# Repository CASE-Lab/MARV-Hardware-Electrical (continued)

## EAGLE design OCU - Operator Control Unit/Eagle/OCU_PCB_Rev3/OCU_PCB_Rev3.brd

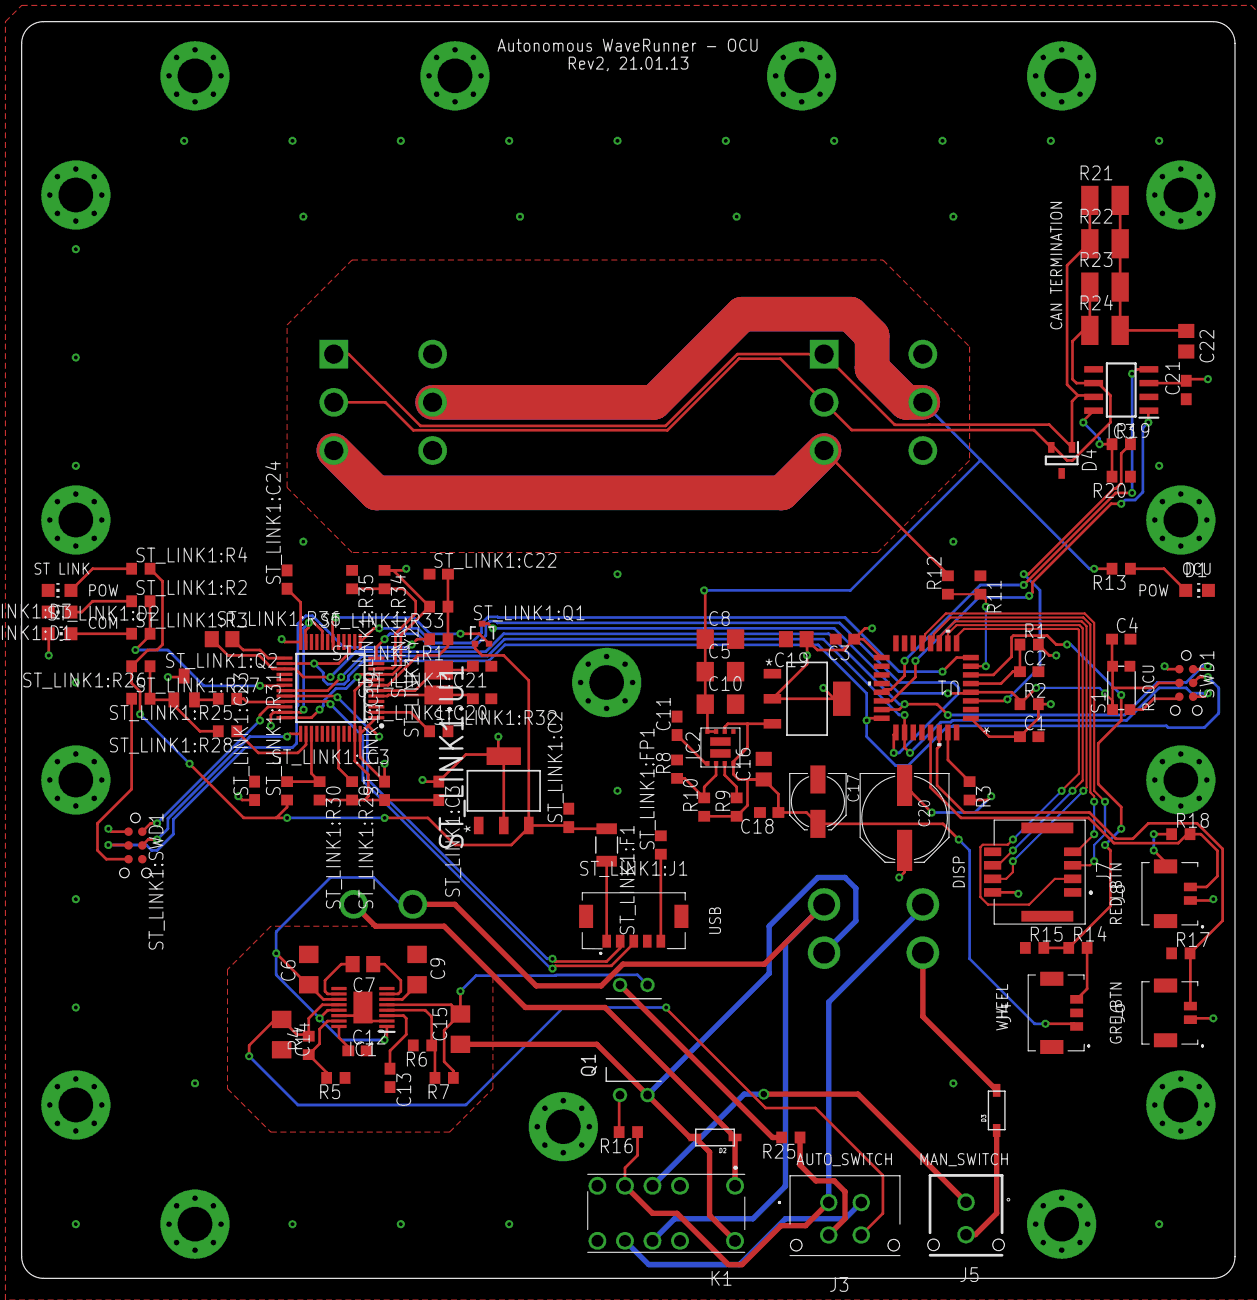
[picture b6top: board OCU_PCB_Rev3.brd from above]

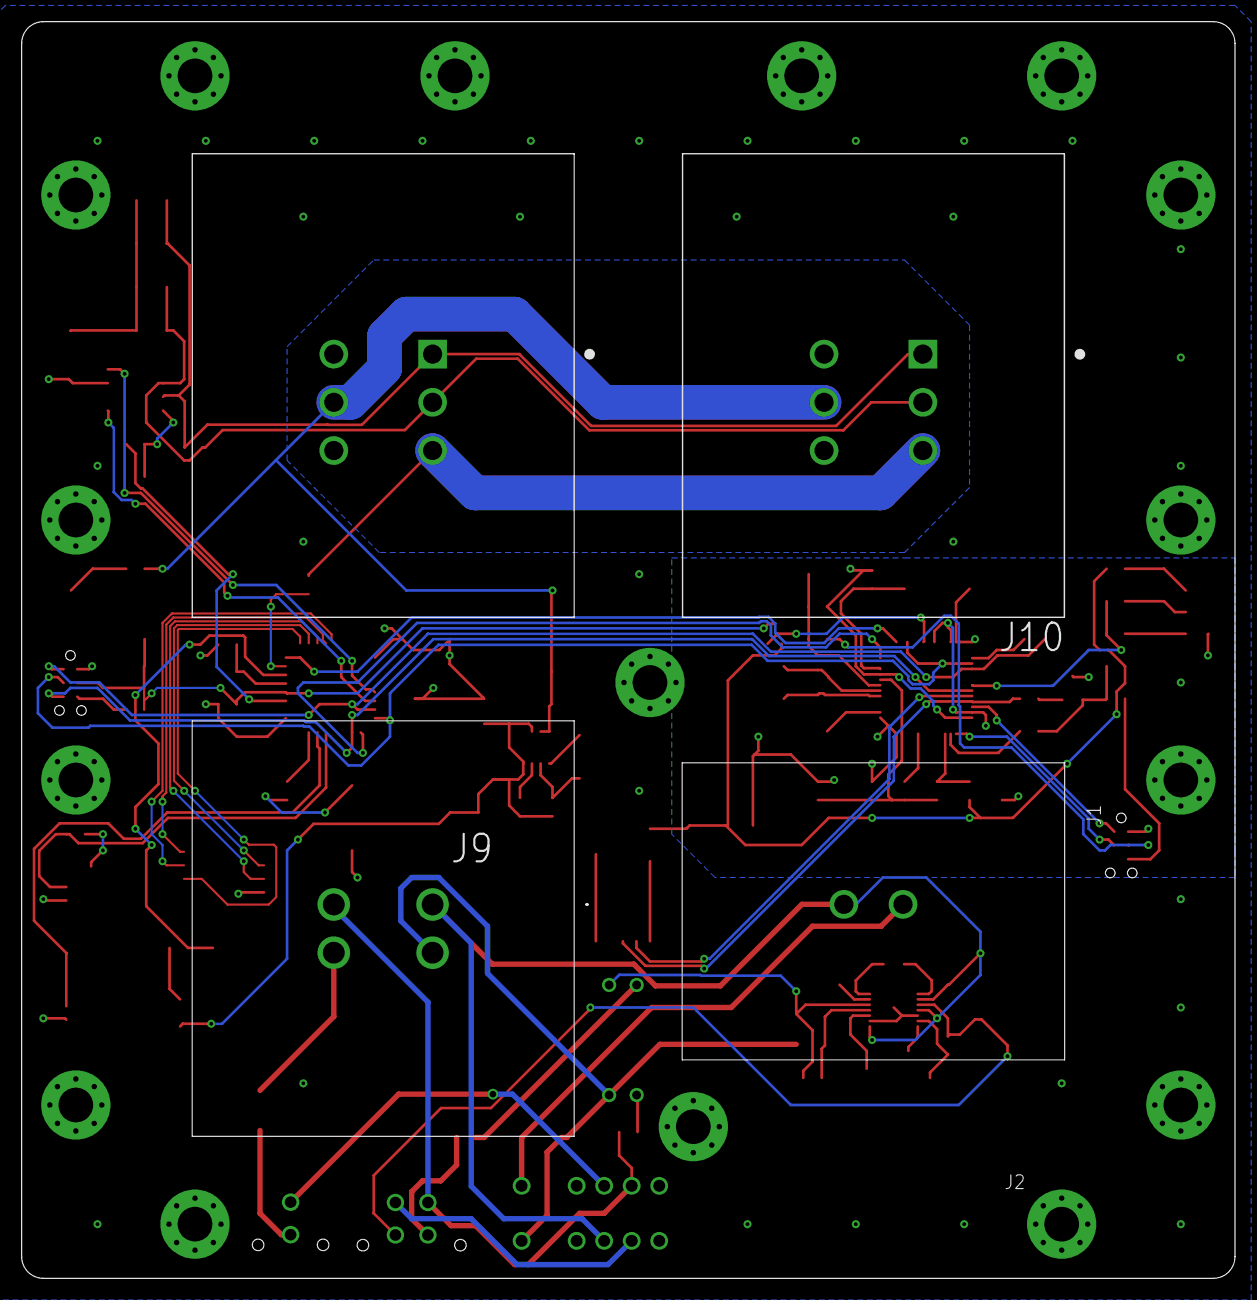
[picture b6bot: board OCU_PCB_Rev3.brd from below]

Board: 2 copper layers, 112.0 x 116.0 mm, 122 parts (4 on the bottom side), 79 nets.

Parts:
C1, C2, C3, C4, C21: 0.1uF; C0603
C5, C6, C8, C9, C10, C14, C15: 10uF; C1206
C7: 1uF; C0805
C11: 3.3nF; C0603
C12, C13: 10nF; C0603
C16: 22uF; C0805
C17: 100uF; PANASONIC_C
C18: 100nF; C0603
C19: 10uF; C0805
C20: 220uF; PANASONIC_E
C22: 4.7nF; C0805
D1: 12V-POW; CHIP-LED0805
D2, D3: SOD-123
D4: SZNUP2105LT1G; SOT96P237X111-3N
HOLE1, HOLE2, HOLE3, HOLE4, HOLE5, HOLE6, HOLE7, HOLE8, HOLE9, HOLE10, HOLE11, HOLE12, HOLE13, HOLE14, HOLE15, HOLE16: M3_MOUNTING_HOLE
IC1: LTC3260EMSE#PBF; SOP50P490X110-17N
IC2: LMZ21700SILT; SIL0008E
IC3: SN65HVD230DR; SOT127P600X175-8N
J1: DT15-2P; DT152P
J2: DT15-4P; DT154P
J3: 43045-0413; 430450413
J4: 505567-0371; 5055680371
J5: 43045-0213
J6, J8: 505567-0271; 5055680271
J7: 505433-0871; 5054330871
J9, J10: DT15-6P; TE_DT15-6P
K1: V23079A1003B301; 413937885
Q1: VO618A-3; DIL04-400
R1: BLM18PG471SN1D; R0603
R2, R3, R17, R18: 10K; R0603
R4, R7: 909K; R0603
R5, R6: 100K; R0603
R8: 44K2 1%; R0603
R9: 10K 1%; R0603
R10: 232K 1%; R0603
R11: 3K9; R0603
R12: 15K; R0603
R13: 820R; R0603
R14: 4K7; R0603
R15: 9K1; R0603
R16: 1K5; R0603
R19: -; R0603
R20, R25: 0R; R0603
R21, R22, R23, R24: 120R; R1210
S1: KMR621NGLFS
ST_LINK1:C2, ST_LINK1:C19, ST_LINK1:C22, ST_LINK1:C23, ST_LINK1:C24: 0.1uF; C0603
ST_LINK1:C3: 10uF; C0603
ST_LINK1:C20, ST_LINK1:C21: 10pF; C0603
ST_LINK1:D1, ST_LINK1:D2, ST_LINK1:D3: CHIP-LED0805
ST_LINK1:F1: OZCJ0050; OZCJ
ST_LINK1:FP1: R0603
ST_LINK1:IC3: STM32F103CBT6TR; QFP50P900X900X160-48N
ST_LINK1:J1: 505568-0571; 5055680571
ST_LINK1:Q1: 2N7002PW,115; SOT323
ST_LINK1:Q2: BC817; SOT23
ST_LINK1:R1: 0; R0603
ST_LINK1:R2, ST_LINK1:R3: 330; R0603
ST_LINK1:R4: 680; R0603
ST_LINK1:R25: 1K5; R0603
ST_LINK1:R26, ST_LINK1:R32: 10K; R0603
ST_LINK1:R27: 36K; R0603
ST_LINK1:R28: 100; R0603
ST_LINK1:R29, ST_LINK1:R33: 100K; R0603
ST_LINK1:R30, ST_LINK1:R34, ST_LINK1:R35: 4K7; R0603
ST_LINK1:R31: 2K7; R0603
ST_LINK1:R36: 100; R0805
ST_LINK1:SWD1: SWD_TAGCONNECTNO-LEG; TC2030-IDC-NL
ST_LINK1:U1: LD1117S33TR; SOT230P700X180-4N
ST_LINK1:Y2: NX3225GD-8MHZ-STD-CRA-3; RESC3226X100N
SWD1: SWD_TAGCONNECTNO-LEG; TC2030-IDC-NL
U1: STM32F303K8; LQFP-32
U2: LD1117S33TR; SOT230P700X180-4N

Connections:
12V: C5.1, C8.1, C10.1, IC2.7, IC2.8, J9.5, J10.5, R13.2
+3V3: C1.1, C3.1, C19.1, C20.+, C21.2, IC3.3, J6.1, J7.2, J8.1, R1.2, R2.2, SWD1.1, U1.1, U1.17, U2.2, U2.4
+5V: C16.1, C17.+, C18.1, IC2.4, IC2.6, J4.1, R9.1, R10.1, U2.3
+12V: J9.3, J10.3, R12.2
+24V: C14.1, IC1.12, J3.4, R4.2
BTN_GRE: J6.2, R17.2, U1.30
BTN_RED: J8.2, R18.2, U1.29
CAN_N: D4.2, IC3.6, J9.2, J10.2, R23.1, R24.1
CAN_N1: D4.1, IC3.7, J9.1, J10.1, R21.1, R22.1
D: IC3.1, U1.22
DISP_CS: J7.6, U1.10
DISP_DC: J7.3, U1.9
DISP_DIN: J7.5, U1.13
DISP_RST: J7.7, U1.12
DISP_SCLK: J7.4, U1.11
GND: C1.2, C2.2, C3.2, C4.2, C5.2, C8.2, C10.2, C11.2, C16.2, C17.-, C18.2, C19.2, C20.-, C21.1, C22.2, D1.C, D4.3, IC2.5, IC2.9, IC2.10, IC3.2, J4.2, J4.MP1, J4.MP2, J6.MP1, J6.MP2, J7.1, J7.MP1, J7.MP2, J8.MP1, J8.MP2, J9.4, J9.6, J10.4, J10.6, R3.2, R8.2, R11.1, R15.1, R17.1, R18.1, R20.1, S1.1, S1.2, ST_LINK1:C2.2, ST_LINK1:C3.2, ST_LINK1:C19.1, ST_LINK1:C20.1, ST_LINK1:C21.1, ST_LINK1:C22.1, ST_LINK1:C23.2, ST_LINK1:C24.2, ST_LINK1:D1.C, ST_LINK1:D3.C, ST_LINK1:FP1.2, ST_LINK1:IC3.8, ST_LINK1:IC3.20, ST_LINK1:IC3.23, ST_LINK1:IC3.35, ST_LINK1:IC3.47, ST_LINK1:J1.4, ST_LINK1:J1.MP1, ST_LINK1:J1.MP2, ST_LINK1:R27.1, ST_LINK1:R29.2, ST_LINK1:R30.2, ST_LINK1:R32.2, ST_LINK1:R35.1, ST_LINK1:SWD1.5, ST_LINK1:U1.1, SWD1.5, U1.16, U1.32, U2.1
GNDA: C15.2, IC1.5, Q1.3, R7.1
MAN_S_IN: J5.1, K1.4
MAN_S_OUT: J2.4, J3.1, K1.5, R16.1
MODE_LED: J3.3, R25.1
unnamed: J4.3, R14.2
unnamed: C7.1, IC1.7
unnamed: C7.2, IC1.10
unnamed: C22.1, R21.2, R22.2, R23.2, R24.2
unnamed: IC2.2, R8.1, R10.2
unnamed: C11.1, IC2.1
unnamed: C12.1, IC1.16
unnamed: C13.1, IC1.3
unnamed: D3.C, J5.2
unnamed: D1.A, R13.1
unnamed: IC2.3, R9.2
unnamed: J3.2, K1.8
unnamed: C9.2, IC1.6
unnamed: IC1.15, R4.1, R5.2
unnamed: IC3.8, R19.1, R20.2
unnamed: IC1.4, R6.1, R7.2
unnamed: Q1.4, R25.2
unnamed: D3.A, J2.3
unnamed: Q1.1, R16.2
unnamed: D2.C, J1.2, K1.1
unnamed: C2.1, R1.1, U1.5
unnamed: R3.1, U1.31
NRST: C4.1, R2.1, S1.3, S1.4, ST_LINK1:Q1.3, SWD1.3, U1.4
R: IC3.4, U1.21
RS: R19.2, U1.3
RX2: ST_LINK1:IC3.12, U1.25
STM_12_INDIC: R11.2, R12.1, U1.7
ST_LINK1:+3V3: ST_LINK1:C3.1, ST_LINK1:C19.2, ST_LINK1:C23.1, ST_LINK1:C24.1, ST_LINK1:D2.A, ST_LINK1:IC3.1, ST_LINK1:IC3.9, ST_LINK1:IC3.24, ST_LINK1:IC3.36, ST_LINK1:IC3.48, ST_LINK1:Q2.3, ST_LINK1:R33.2, ST_LINK1:R34.1, ST_LINK1:SWD1.1, ST_LINK1:U1.2, ST_LINK1:U1.4
ST_LINK1:+5V: ST_LINK1:C2.1, ST_LINK1:F1.1, ST_LINK1:Q1.1, ST_LINK1:R4.2, ST_LINK1:R26.2, ST_LINK1:R31.1, ST_LINK1:U1.3
ST_LINK1:N$1: ST_LINK1:D1.A, ST_LINK1:R2.1
ST_LINK1:N$2: ST_LINK1:D3.A, ST_LINK1:R4.1
ST_LINK1:N$3: ST_LINK1:D2.C, ST_LINK1:R3.1
ST_LINK1:N$4: ST_LINK1:FP1.1, ST_LINK1:J1.5
ST_LINK1:N$7: ST_LINK1:Q2.2, ST_LINK1:R25.2
ST_LINK1:N$8: ST_LINK1:Q2.1, ST_LINK1:R26.1, ST_LINK1:R27.2, ST_LINK1:R28.2
ST_LINK1:N$15: ST_LINK1:IC3.39, ST_LINK1:R30.1, ST_LINK1:R31.2
ST_LINK1:N$16: ST_LINK1:IC3.2, ST_LINK1:R32.1
ST_LINK1:N$21: ST_LINK1:IC3.44, ST_LINK1:R29.1
ST_LINK1:N$22: ST_LINK1:C20.2, ST_LINK1:IC3.5, ST_LINK1:Y2.1
ST_LINK1:N$23: ST_LINK1:IC3.10, ST_LINK1:R34.2, ST_LINK1:R35.2
ST_LINK1:N$24: ST_LINK1:C21.2, ST_LINK1:IC3.6, ST_LINK1:Y2.2
ST_LINK1:N$25: ST_LINK1:C22.2, ST_LINK1:IC3.7, ST_LINK1:R1.1, ST_LINK1:R33.1
ST_LINK1:N$26: ST_LINK1:IC3.25, ST_LINK1:R36.2
ST_LINK1:N$27: ST_LINK1:F1.2, ST_LINK1:J1.1
ST_LINK1:NRST: ST_LINK1:IC3.18, ST_LINK1:Q1.2
ST_LINK1:STLK_LED: ST_LINK1:IC3.30, ST_LINK1:R2.2, ST_LINK1:R3.2
ST_LINK1:STM_NRST: ST_LINK1:R1.2, ST_LINK1:SWD1.3
ST_LINK1:STM_SWCLK: ST_LINK1:IC3.37, ST_LINK1:SWD1.4
ST_LINK1:STM_SWDIO: ST_LINK1:IC3.34, ST_LINK1:SWD1.2
ST_LINK1:USB_D_N: ST_LINK1:IC3.32, ST_LINK1:J1.2
ST_LINK1:USB_D_P: ST_LINK1:IC3.33, ST_LINK1:J1.3, ST_LINK1:R25.1
ST_LINK1:USB_RENUM: ST_LINK1:IC3.38, ST_LINK1:R28.1
SWDCLK: ST_LINK1:IC3.15, ST_LINK1:IC3.26, SWD1.4, U1.24
SWDIO: ST_LINK1:IC3.27, ST_LINK1:R36.1, SWD1.2, U1.23
SWO: ST_LINK1:IC3.31, SWD1.6, U1.26
S_12V: C6.1, IC1.1, IC1.11, IC1.13, J1.1, J2.1, K1.9
S_GND: C6.2, C9.1, C12.2, C13.2, C14.2, C15.1, D2.A, IC1.2, IC1.14, IC1.17, J2.2, K1.12, Q1.2, R5.1, R6.2
TX2: ST_LINK1:IC3.13, U1.8
WHEEL: R14.1, R15.2, U1.6

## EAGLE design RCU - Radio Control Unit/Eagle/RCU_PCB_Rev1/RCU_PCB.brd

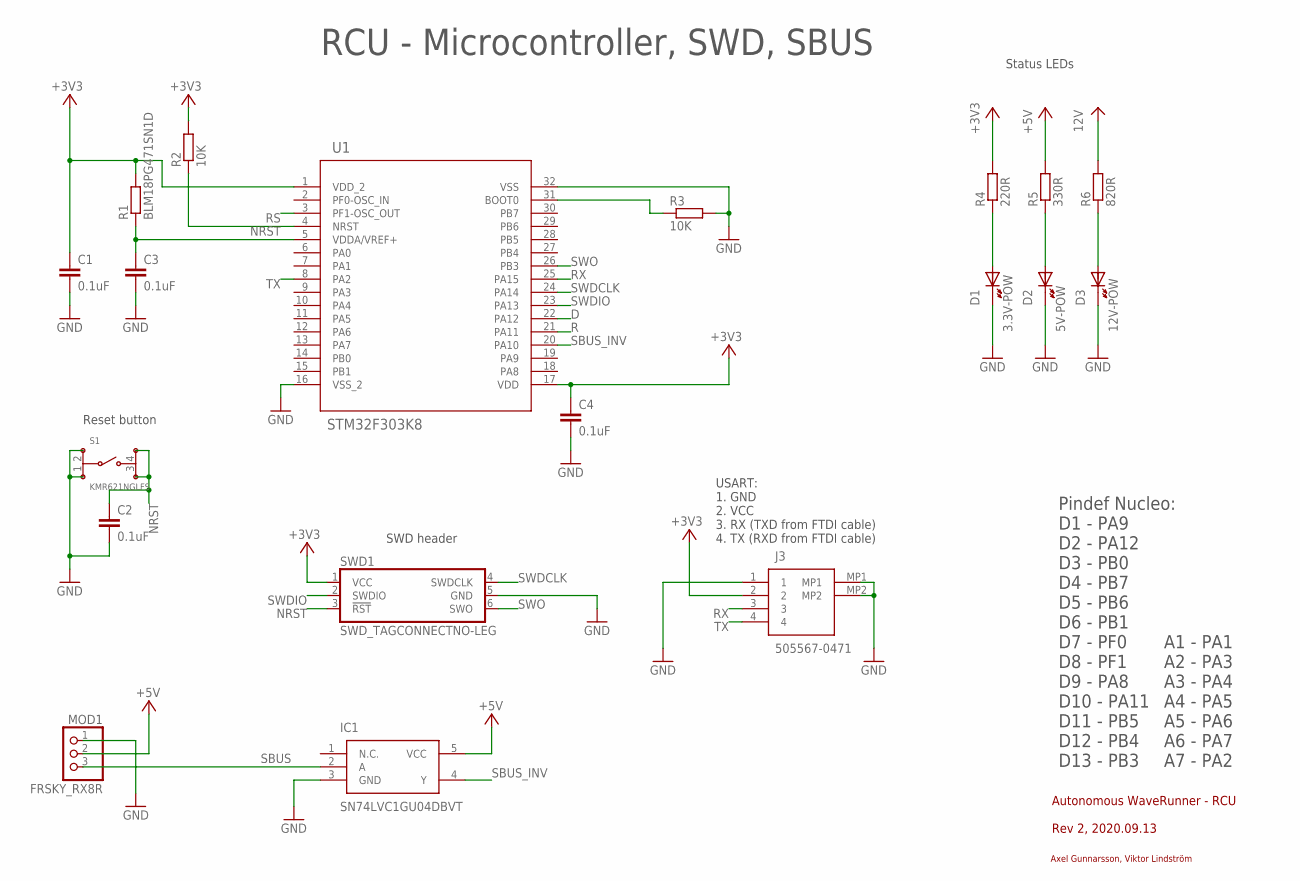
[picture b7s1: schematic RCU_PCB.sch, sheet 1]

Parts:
C1, C2, C3, C4: 0.1uF; C0603
D1: 3.3V-POW; CHIP-LED0805
D2: 5V-POW; CHIP-LED0805
D3: 12V-POW; CHIP-LED0805
IC1: SN74LVC1GU04DBVT; SOT95P280X145-5N
J3: 505567-0471; 5055680471
MOD1: FRSKY_RX8R
R1: BLM18PG471SN1D; R0603
R2, R3: 10K; R0603
R4: 220R; R0603
R5: 330R; R0603
R6: 820R; R0603
S1: KMR621NGLFS
SWD1: SWD_TAGCONNECTNO-LEG; TC2030-IDC-NL
U1: STM32F303K8; LQFP-32

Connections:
12V: R6.2; also elsewhere on the board
+3V3: C1.1, C4.1, J3.2, R1.2, R2.2, R4.2, SWD1.1 (VCC), U1.1 (VDD_2), U1.17 (VDD); also elsewhere on the board
+5V: IC1.5 (VCC), MOD1.2, R5.2; also elsewhere on the board
D: U1.22 (PA12); also elsewhere on the board
GND: C1.2, C2.2, C3.2, C4.2, D1.C (K), D2.C (K), D3.C (K), IC1.3 (GND), J3.1, J3.MP1, J3.MP2, MOD1.1, R3.2, S1.1, S1.2, SWD1.5 (GND), U1.16 (VSS_2), U1.32 (VSS); also elsewhere on the board
unnamed: D3.A, R6.1
unnamed: D2.A, R5.1
unnamed: C3.1, R1.1, U1.5 (VDDA/VREF+)
unnamed: D1.A, R4.1
unnamed: R3.1, U1.31 (BOOT0)
NRST: C2.1, R2.1, S1.3, S1.4, SWD1.3 (!RST), U1.4 (NRST)
R: U1.21 (PA11); also elsewhere on the board
RS: U1.3 (PF1-OSC_OUT); also elsewhere on the board
RX: J3.3, U1.25 (PA15)
SBUS: IC1.2 (A), MOD1.3
SBUS_INV: IC1.4 (Y), U1.20 (PA10)
SWDCLK: SWD1.4 (SWDCLK), U1.24 (PA14)
SWDIO: SWD1.2 (SWDIO), U1.23 (PA13)
SWO: SWD1.6 (SWO), U1.26 (PB3)
TX: J3.4, U1.8 (PA2)

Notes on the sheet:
Autonomous WaveRunner - RCU
Rev 2, 2020.09.13
Axel Gunnarsson, Viktor Lindström
RCU - Microcontroller, SWD, SBUS
SWD header
Reset button
Pindef Nucleo: D1 - PA9 D2 - PA12 D3 - PB0 D4 - PB7 D5 - PB6 D6 - PB1 D7 - PF0 D8 - PF1 D9 - PA8 D10 - PA11 D11 - PB5 D12 - PB4 D13 - PB3
A1 - PA1 A2 - PA3 A3 - PA4 A4 - PA5 A5 - PA6 A6 - PA7 A7 - PA2
Status LEDs
USART: 1. GND 2. VCC 3. RX (TXD from FTDI cable) 4. TX (RXD from FTDI cable)

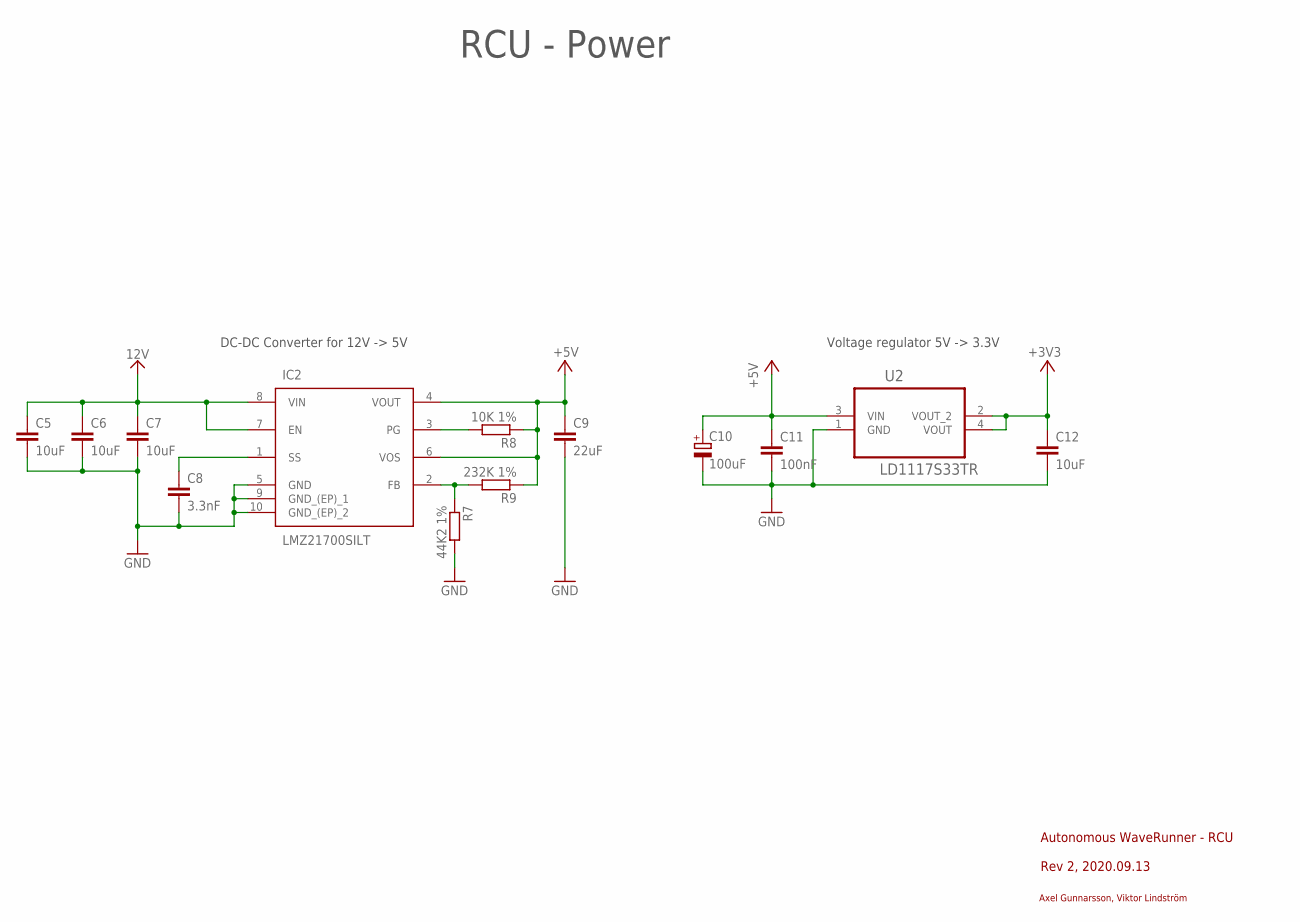
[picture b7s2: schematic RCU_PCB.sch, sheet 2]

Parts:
C5, C6, C7: 10uF; C1206
C8: 3.3nF; C0603
C9: 22uF; C0805
C10: 100uF; PANASONIC_C
C11: 100nF; C0603
C12: 10uF; C0805
IC2: LMZ21700SILT; SIL0008E
R7: 44K2 1%; R0603
R8: 10K 1%; R0603
R9: 232K 1%; R0603
U2: LD1117S33TR; SOT230P700X180-4N

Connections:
12V: C5.1, C6.1, C7.1, IC2.7 (EN), IC2.8 (VIN); also elsewhere on the board
+3V3: C12.1, U2.2 (VOUT_2), U2.4 (VOUT); also elsewhere on the board
+5V: C9.1, C10.+, C11.1, IC2.4 (VOUT), IC2.6 (VOS), R8.1, R9.1, U2.3 (VIN); also elsewhere on the board
GND: C5.2, C6.2, C7.2, C8.2, C9.2, C10.-, C11.2, C12.2, IC2.5 (GND), IC2.9 (GND_(EP)_1), IC2.10 (GND_(EP)_2), R7.2, U2.1 (GND); also elsewhere on the board
unnamed: IC2.2 (FB), R7.1, R9.2
unnamed: C8.1, IC2.1 (SS)
unnamed: IC2.3 (PG), R8.2

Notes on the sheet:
DC-DC Converter for 12V -> 5V
Voltage regulator 5V -> 3.3V
Autonomous WaveRunner - RCU
Rev 2, 2020.09.13
Axel Gunnarsson, Viktor Lindström
RCU - Power

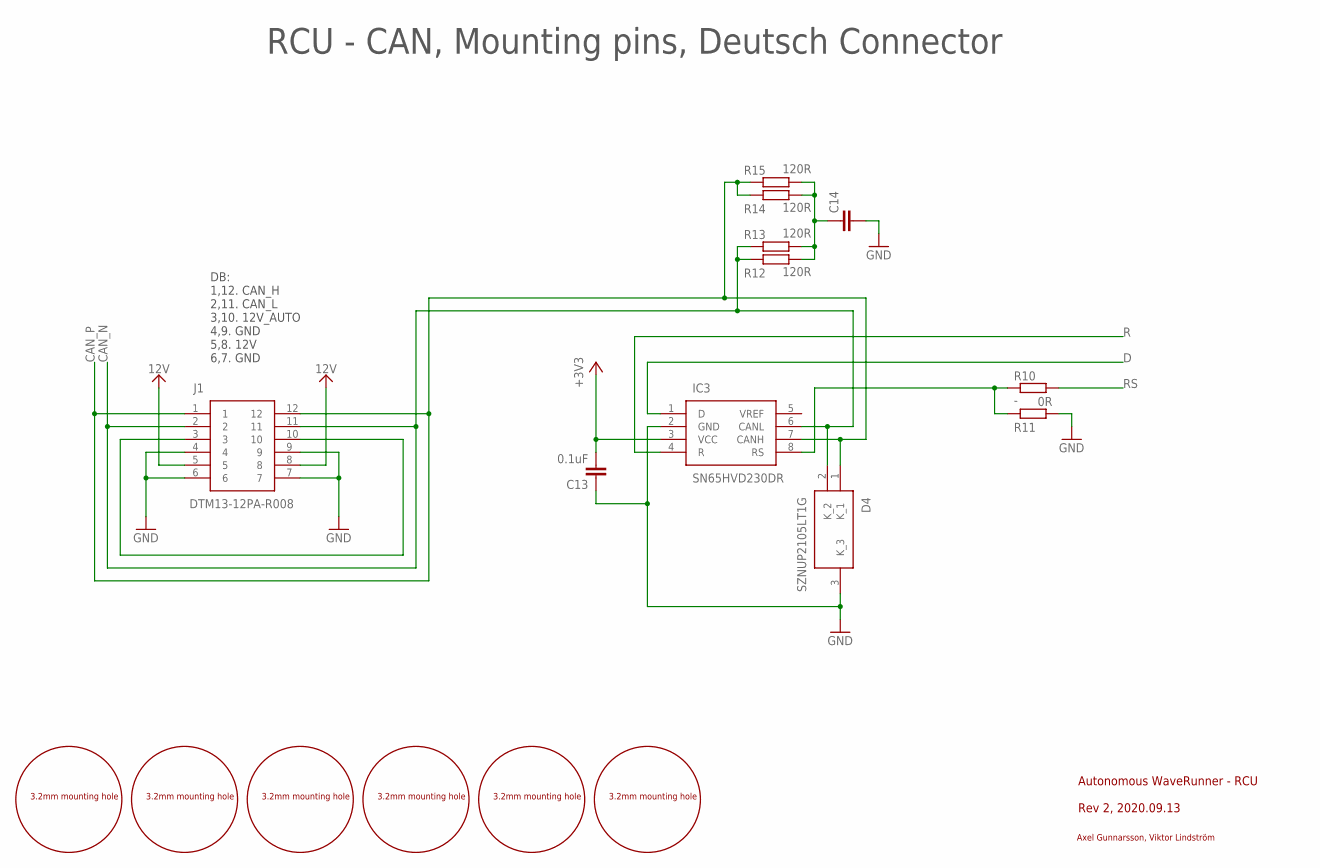
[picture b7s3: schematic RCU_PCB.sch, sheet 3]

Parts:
C13: 0.1uF; C0603
C14: C0805
D4: SZNUP2105LT1G; SOT96P237X111-3N
HOLE1, HOLE2, HOLE3, HOLE4, HOLE5, HOLE6: M3_MOUNTING_HOLE
IC3: SN65HVD230DR; SOT127P600X175-8N
J1: DTM13-12PA-R008; DTM1312PAR008
R10: -; R0603
R11: 0R; R0603
R12, R13, R14, R15: 120R; R1210

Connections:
12V: J1.5, J1.8; also elsewhere on the board
+3V3: C13.2, IC3.3 (VCC); also elsewhere on the board
CAN_N: D4.2 (K_2), IC3.6 (CANL), J1.2, J1.11, R12.1, R13.1
CAN_P: D4.1 (K_1), IC3.7 (CANH), J1.1, J1.12, R14.1, R15.1
D: IC3.1 (D); also elsewhere on the board
GND: C13.1, C14.2, D4.3 (K_3), IC3.2 (GND), J1.4, J1.6, J1.7, J1.9, R11.1; also elsewhere on the board
unnamed: C14.1, R12.2, R13.2, R14.2, R15.2
unnamed: J1.3, J1.10
unnamed: IC3.8 (RS), R10.1, R11.2
R: IC3.4 (R); also elsewhere on the board
RS: R10.2; also elsewhere on the board

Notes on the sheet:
DB: 1,12. CAN_H 2,11. CAN_L 3,10. 12V_AUTO 4,9. GND 5,8. 12V 6,7. GND
Autonomous WaveRunner - RCU
Rev 2, 2020.09.13
Axel Gunnarsson, Viktor Lindström
RCU - CAN, Mounting pins, Deutsch Connector

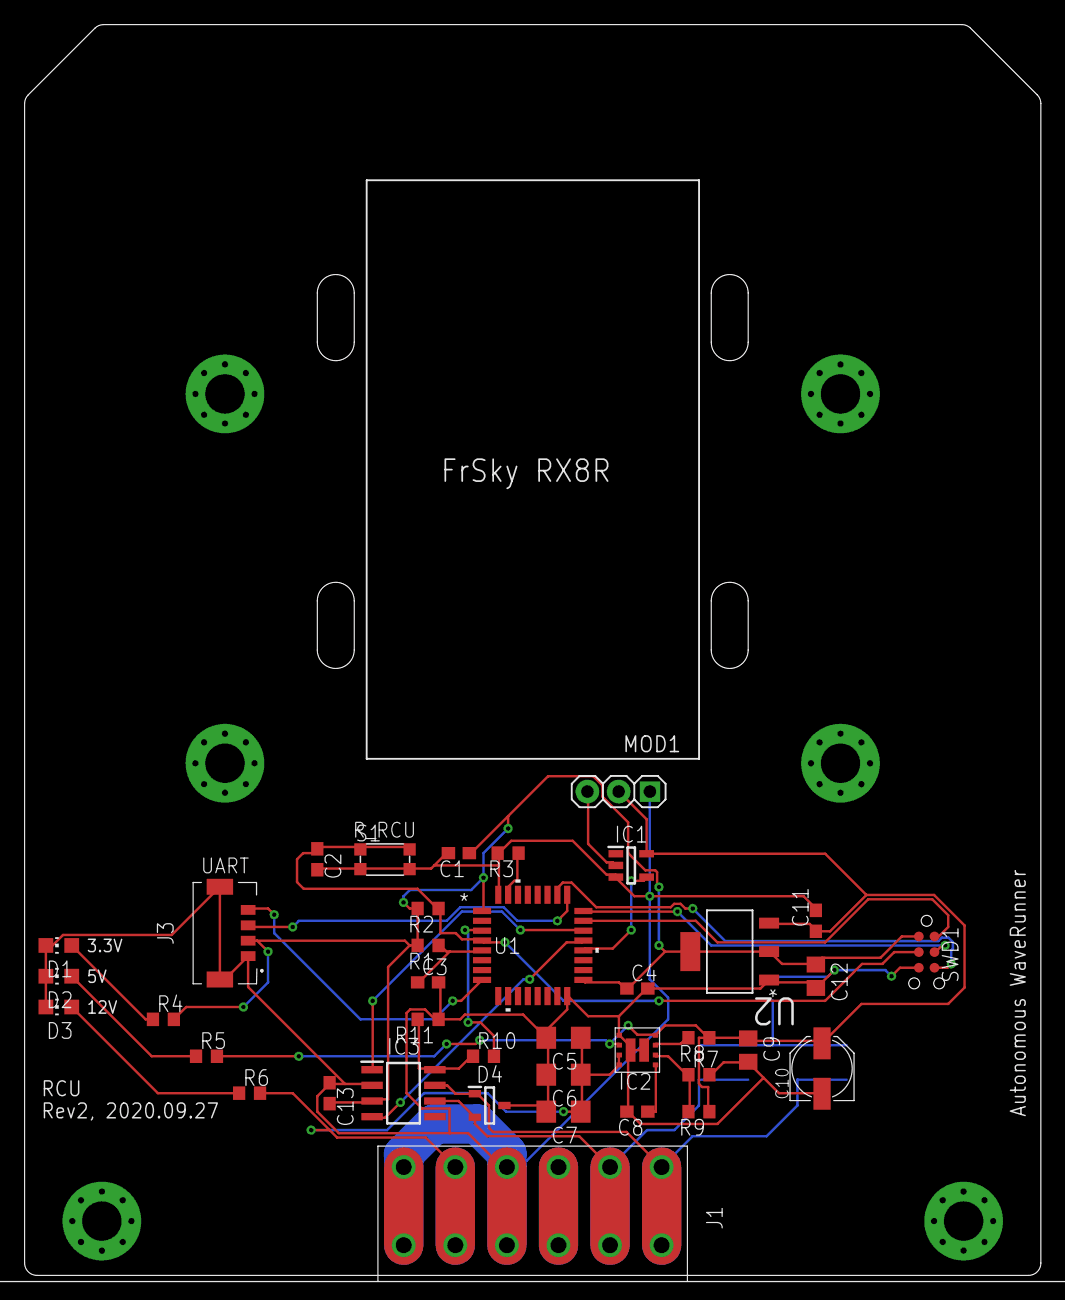
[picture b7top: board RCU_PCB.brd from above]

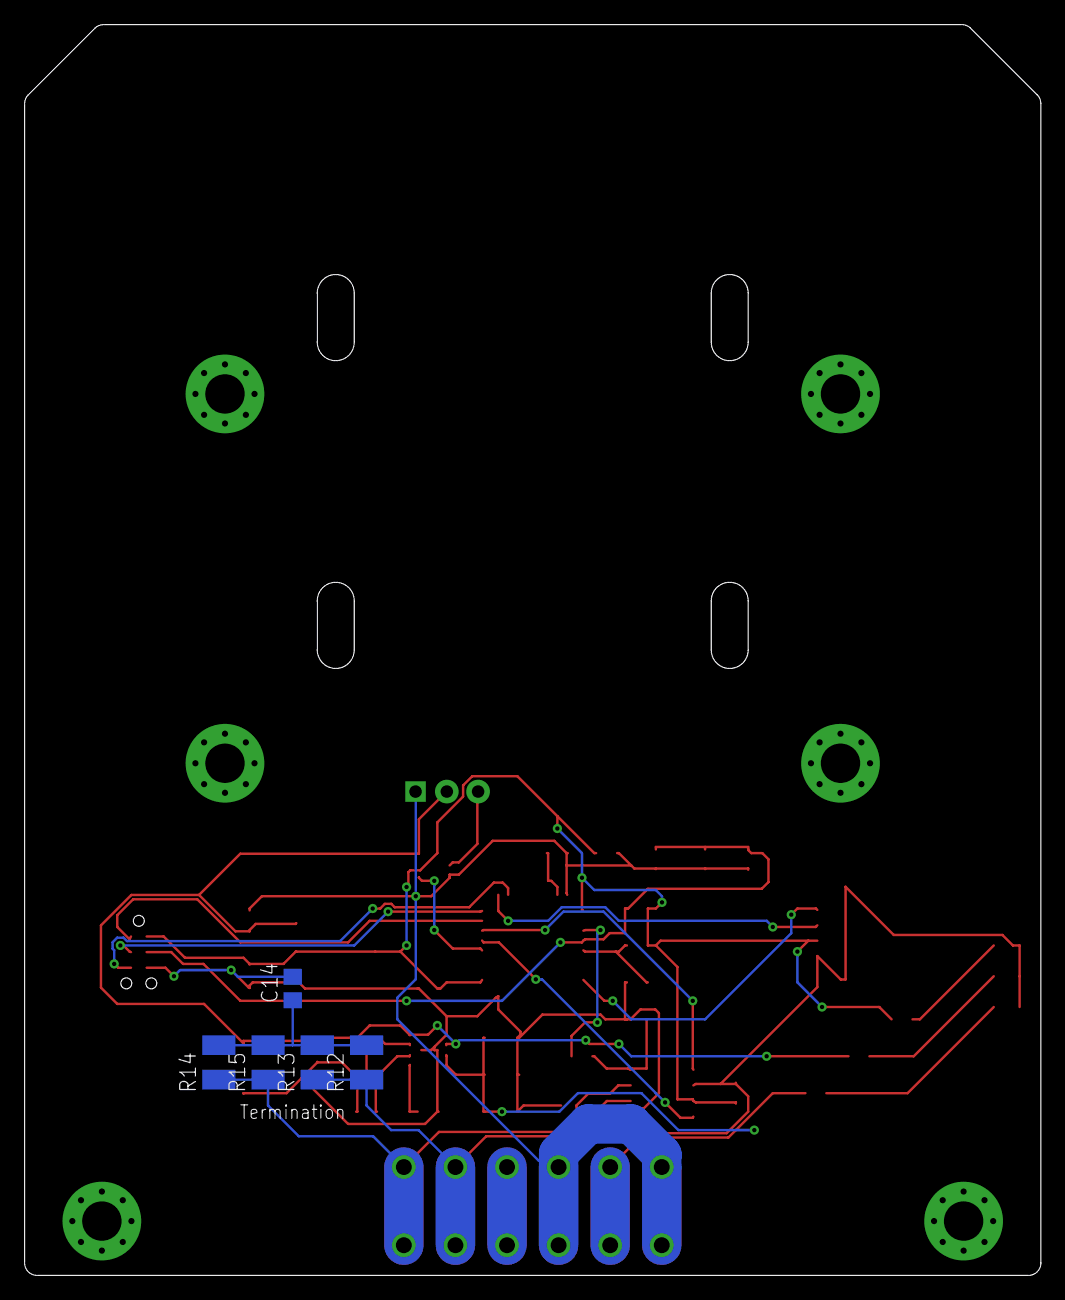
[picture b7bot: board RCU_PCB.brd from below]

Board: 2 copper layers, 82.5 x 101.6 mm, 49 parts (5 on the bottom side), 28 nets.

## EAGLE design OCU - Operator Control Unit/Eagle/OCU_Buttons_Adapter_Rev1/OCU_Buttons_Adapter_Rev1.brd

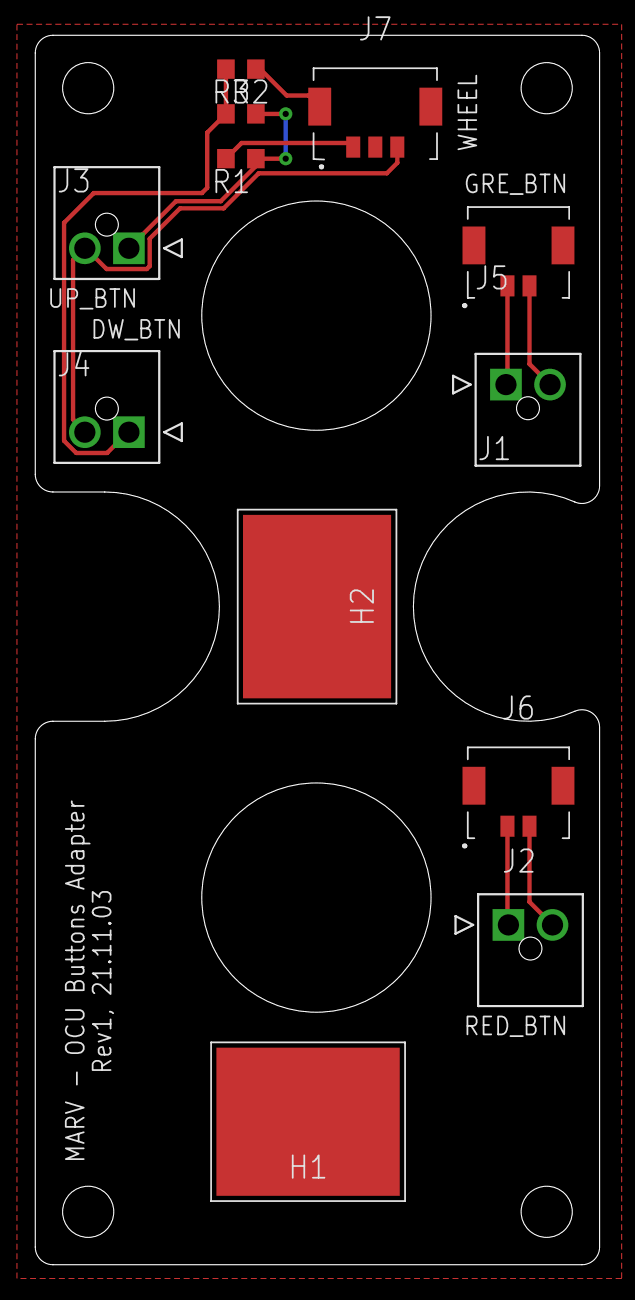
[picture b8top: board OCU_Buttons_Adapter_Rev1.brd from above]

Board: 2 copper layers, 32.0 x 69.7 mm, 12 parts (0 on the bottom side), 9 nets.

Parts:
H1, H2: S8131-46R; S813146R
J1, J2, J3, J4: 1053091202; 1053091402
J5, J6: 505567-0271; 5055680271
J7: 505567-0371; 5055680371
R1, R2, R3: 2K; R0603

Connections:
GND: H1.1, H2.1, J5.MP1, J5.MP2, J6.MP1, J6.MP2, J7.2, J7.MP1, J7.MP2, R3.1
unnamed: J1.1, J5.1
unnamed: J1.2, J5.2
unnamed: J2.1, J6.1
unnamed: J2.2, J6.2
unnamed: J3.1, R1.1, R2.2
unnamed: J4.1, R2.1, R3.2
unnamed: J3.2, J4.2, J7.3
unnamed: J7.1, R1.2

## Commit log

2021-09-12 Create LICENSE
2021-11-03 added OCU top buttons to exsisting hardware adapter
2021-11-03 finished button adapter, started with power pcb
2021-11-05 finished board
2021-12-09 updated MCU power pcb
2022-08-03 Added LED driver PCBA
2022-08-22 added ibom files
